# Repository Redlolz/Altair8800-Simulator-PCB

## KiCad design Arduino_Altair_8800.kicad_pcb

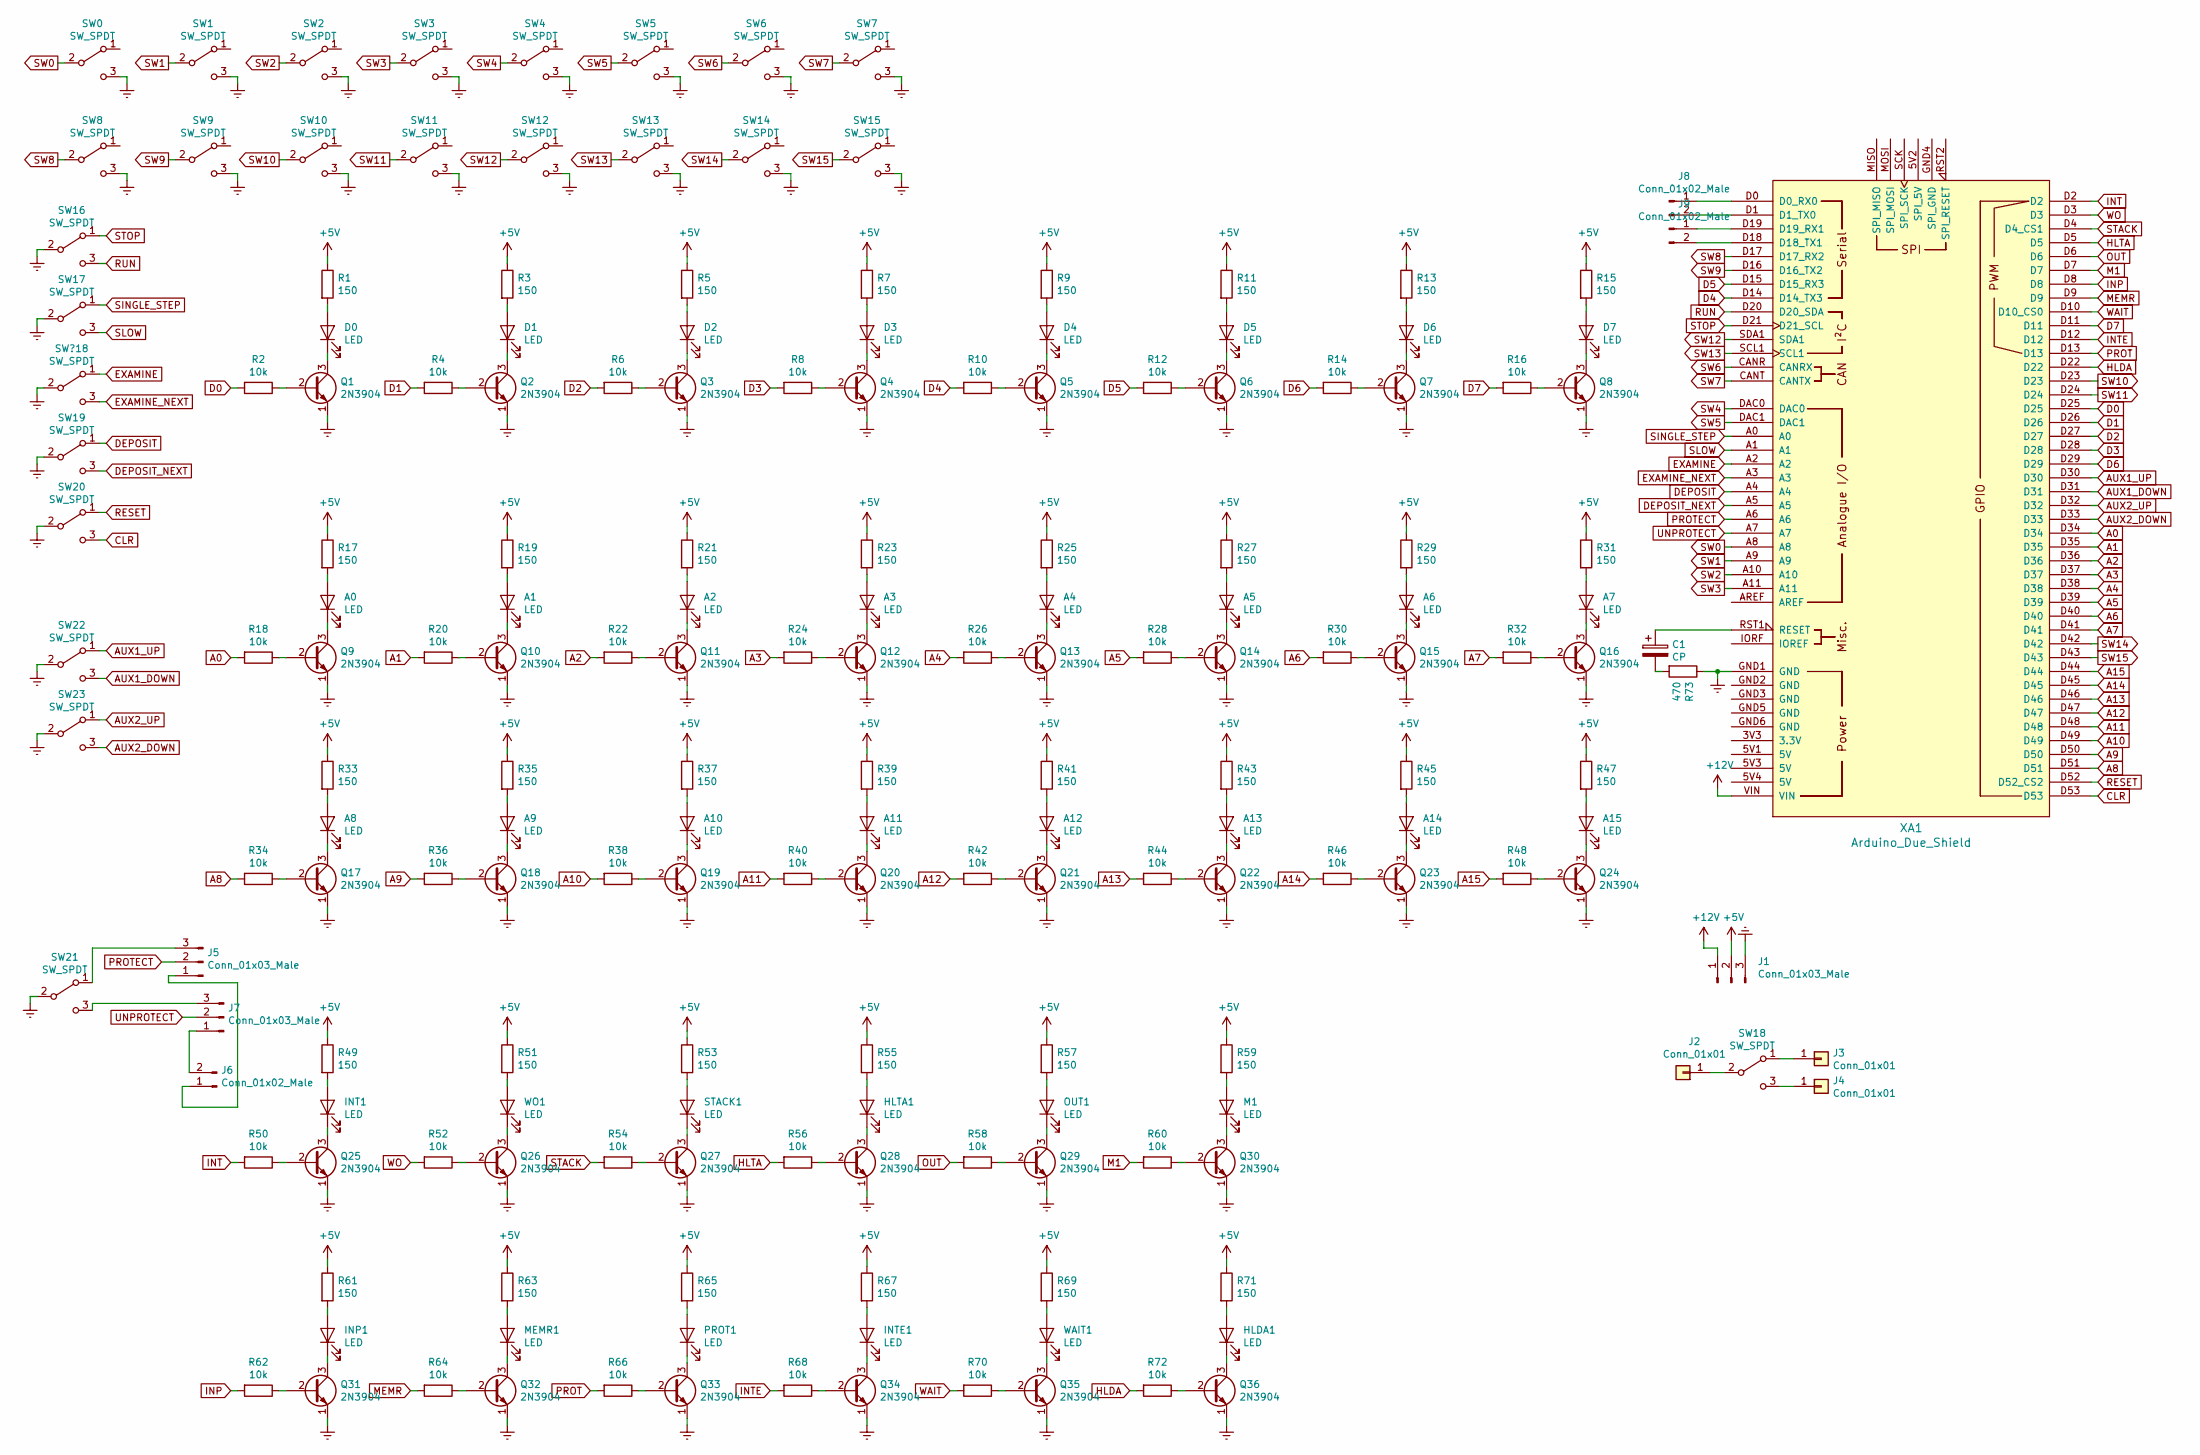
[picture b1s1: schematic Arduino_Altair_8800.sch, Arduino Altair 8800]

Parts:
A0, A1, A2, A3, A4, A5, A6, A7, A8, A9, A10, A11, A12, A13, A14, A15: LED; LED_D5.0mm
C1: CP; CP_Radial_D4.0mm_P1.50mm
D0, D1, D2, D3, D4, D5, D6, D7: LED; LED_D5.0mm
HLDA1: LED; LED_D5.0mm
HLTA1: LED; LED_D5.0mm
INP1: LED; LED_D5.0mm
INT1: LED; LED_D5.0mm
INTE1: LED; LED_D5.0mm
J1: Conn_01x03_Male; PinSocket_1x03_P2.54mm_Vertical
J2, J3, J4: Conn_01x01; SolderWirePad_1x01_Drill2mm
J5, J7: Conn_01x03_Male; PinHeader_1x03_P2.54mm_Vertical
J6, J8, J9: Conn_01x02_Male; PinHeader_1x02_P2.54mm_Vertical
M1: LED; LED_D5.0mm
MEMR1: LED; LED_D5.0mm
OUT1: LED; LED_D5.0mm
PROT1: LED; LED_D5.0mm
Q1, Q2, Q3, Q4, Q5, Q6, Q7, Q8, Q9, Q10, Q11, Q12, Q13, Q14, Q15, Q16, Q17, Q18, Q19, Q20, Q21, Q22, Q23, Q24, Q25, Q26, Q27, Q28, Q29, Q30, Q31, Q32, Q33, Q34, Q35, Q36: 2N3904; TO-92_Inline
R1, R3, R5, R7, R9, R11, R13, R15, R17, R19, R21, R23, R25, R27, R29, R31, R33, R35, R37, R39, R41, R43, R45, R47, R49, R51, R53, R55, R57, R59, R61, R63, R65, R67, R69, R71: 150; R_Axial_DIN0207_L6.3mm_D2.5mm_P7.62mm_Horizontal
R2, R4, R6, R8, R10, R12, R14, R16, R18, R20, R22, R24, R26, R28, R30, R32, R34, R36, R38, R40, R42, R44, R46, R48, R50, R52, R54, R56, R58, R60, R62, R64, R66, R68, R70, R72: 10k; R_Axial_DIN0207_L6.3mm_D2.5mm_P7.62mm_Horizontal
R73: 470; R_Axial_DIN0207_L6.3mm_D2.5mm_P7.62mm_Horizontal
STACK1: LED; LED_D5.0mm
SW0, SW1, SW2, SW3, SW4, SW5, SW6, SW7, SW8, SW9, SW10, SW11, SW12, SW13, SW14, SW15, SW16, SW17, SW18, SW19, SW20, SW21, SW22, SW23: SW_SPDT; SPDT_TOGGLE_SW
SW?18: SW_SPDT; SPDT_TOGGLE_SW
WAIT1: LED; LED_D5.0mm
WO1: LED; LED_D5.0mm
XA1: Arduino_Due_Shield

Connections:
+5V: J1.2, R1.1, R3.1, R5.1, R7.1, R9.1, R11.1, R13.1, R15.1, R17.1, R19.1, R21.1, R23.1, R25.1, R27.1, R29.1, R31.1, R33.1, R35.1, R37.1, R39.1, R41.1, R43.1, R45.1, R47.1, R49.1, R51.1, R53.1, R55.1, R57.1, R59.1, R61.1, R63.1, R65.1, R67.1, R69.1, R71.1
+12V: J1.1, XA1.VIN
A0: R18.2, XA1.D34
A1: R20.2, XA1.D35
A2: R22.2, XA1.D36
A3: R24.2, XA1.D37
A4: R26.2, XA1.D38
A5: R28.2, XA1.D39
A6: R30.2, XA1.D40
A7: R32.2, XA1.D41
A8: R34.2, XA1.D51
A9: R36.2, XA1.D50
A10: R38.2, XA1.D49
A11: R40.2, XA1.D48
A12: R42.2, XA1.D47
A13: R44.2, XA1.D46
A14: R46.2, XA1.D45
A15: R48.2, XA1.D44
AUX1_DOWN: SW22.3 (C), XA1.D31
AUX1_UP: SW22.1 (A), XA1.D30
AUX2_DOWN: SW23.3 (C), XA1.D33
AUX2_UP: SW23.1 (A), XA1.D32
CLR: SW20.3 (C), XA1.D53
D0: R2.2, XA1.D25
D1: R4.2, XA1.D26
D2: R6.2, XA1.D27
D3: R8.2, XA1.D28
D4: R10.2, XA1.D14 (D14_TX3)
D5: R12.2, XA1.D15 (D15_RX3)
D6: R14.2, XA1.D29
D7: R16.2, XA1.D11
DEPOSIT: SW19.1 (A), XA1.A4
DEPOSIT_NEXT: SW19.3 (C), XA1.A5
EXAMINE: SW?18.1 (A), XA1.A2
EXAMINE_NEXT: SW?18.3 (C), XA1.A3
Earth: J1.3, Q1.1 (E), Q2.1 (E), Q3.1 (E), Q4.1 (E), Q5.1 (E), Q6.1 (E), Q7.1 (E), Q8.1 (E), Q9.1 (E), Q10.1 (E), Q11.1 (E), Q12.1 (E), Q13.1 (E), Q14.1 (E), Q15.1 (E), Q16.1 (E), Q17.1 (E), Q18.1 (E), Q19.1 (E), Q20.1 (E), Q21.1 (E), Q22.1 (E), Q23.1 (E), Q24.1 (E), Q25.1 (E), Q26.1 (E), Q27.1 (E), Q28.1 (E), Q29.1 (E), Q30.1 (E), Q31.1 (E), Q32.1 (E), Q33.1 (E), Q34.1 (E), Q35.1 (E), Q36.1 (E), R73.1, SW0.3 (C), SW1.3 (C), SW2.3 (C), SW3.3 (C), SW4.3 (C), SW5.3 (C), SW6.3 (C), SW7.3 (C), SW8.3 (C), SW9.3 (C), SW10.3 (C), SW11.3 (C), SW12.3 (C), SW13.3 (C), SW14.3 (C), SW15.3 (C), SW16.2 (B), SW17.2 (B), SW19.2 (B), SW20.2 (B), SW21.2 (B), SW22.2 (B), SW23.2 (B), SW?18.2 (B), XA1.GND1 (GND)
HLDA: R72.2, XA1.D22
HLTA: R56.2, XA1.D5
INP: R62.2, XA1.D8
INT: R50.2, XA1.D2
INTE: R68.2, XA1.D12
M1: R60.2, XA1.D7
MEMR: R64.2, XA1.D9
unnamed: A0.1 (K), Q9.3 (C)
unnamed: A0.2 (A), R17.2
unnamed: A1.1 (K), Q10.3 (C)
unnamed: A1.2 (A), R19.2
unnamed: A2.1 (K), Q11.3 (C)
unnamed: A2.2 (A), R21.2
unnamed: A3.1 (K), Q12.3 (C)
unnamed: A3.2 (A), R23.2
unnamed: A4.1 (K), Q13.3 (C)
unnamed: A4.2 (A), R25.2
unnamed: A5.1 (K), Q14.3 (C)
unnamed: A5.2 (A), R27.2
unnamed: A6.1 (K), Q15.3 (C)
unnamed: A6.2 (A), R29.2
unnamed: A7.1 (K), Q16.3 (C)
unnamed: A7.2 (A), R31.2
unnamed: A8.1 (K), Q17.3 (C)
unnamed: A8.2 (A), R33.2
unnamed: A9.1 (K), Q18.3 (C)
unnamed: A9.2 (A), R35.2
unnamed: A10.1 (K), Q19.3 (C)
unnamed: A10.2 (A), R37.2
unnamed: A11.1 (K), Q20.3 (C)
unnamed: A11.2 (A), R39.2
unnamed: A12.1 (K), Q21.3 (C)
unnamed: A12.2 (A), R41.2
unnamed: A13.1 (K), Q22.3 (C)
unnamed: A13.2 (A), R43.2
unnamed: A14.1 (K), Q23.3 (C)
unnamed: A14.2 (A), R45.2
unnamed: A15.1 (K), Q24.3 (C)
unnamed: A15.2 (A), R47.2
unnamed: C1.1, XA1.RST1 (RESET)
unnamed: C1.2, R73.2
unnamed: D0.1 (K), Q1.3 (C)
unnamed: D0.2 (A), R1.2
unnamed: D1.1 (K), Q2.3 (C)
unnamed: D1.2 (A), R3.2
unnamed: D2.1 (K), Q3.3 (C)
unnamed: D2.2 (A), R5.2
unnamed: D3.1 (K), Q4.3 (C)
unnamed: D3.2 (A), R7.2
unnamed: D4.1 (K), Q5.3 (C)
unnamed: D4.2 (A), R9.2
unnamed: D5.1 (K), Q6.3 (C)
unnamed: D5.2 (A), R11.2
unnamed: D6.1 (K), Q7.3 (C)
unnamed: D6.2 (A), R13.2
unnamed: D7.1 (K), Q8.3 (C)
unnamed: D7.2 (A), R15.2
unnamed: HLDA1.1 (K), Q36.3 (C)
unnamed: HLDA1.2 (A), R71.2
unnamed: HLTA1.1 (K), Q28.3 (C)
unnamed: HLTA1.2 (A), R55.2
unnamed: INP1.1 (K), Q31.3 (C)
unnamed: INP1.2 (A), R61.2
unnamed: INT1.1 (K), Q25.3 (C)
unnamed: INT1.2 (A), R49.2
unnamed: INTE1.1 (K), Q34.3 (C)
unnamed: INTE1.2 (A), R67.2
unnamed: J2.1, SW18.2 (B)
unnamed: J3.1, SW18.1 (A)
unnamed: J4.1, SW18.3 (C)
unnamed: J5.1, J6.1
unnamed: J5.3, SW21.1 (A)
unnamed: J6.2, J7.1
unnamed: J7.3, SW21.3 (C)
unnamed: J8.1, XA1.D0 (D0_RX0)
unnamed: J8.2, XA1.D1 (D1_TX0)
unnamed: J9.1, XA1.D19 (D19_RX1)
unnamed: J9.2, XA1.D18 (D18_TX1)
unnamed: M1.1 (K), Q30.3 (C)
unnamed: M1.2 (A), R59.2
unnamed: MEMR1.1 (K), Q32.3 (C)
unnamed: MEMR1.2 (A), R63.2
unnamed: OUT1.1 (K), Q29.3 (C)
unnamed: OUT1.2 (A), R57.2
unnamed: PROT1.1 (K), Q33.3 (C)
unnamed: PROT1.2 (A), R65.2
unnamed: Q1.2 (B), R2.1
unnamed: Q2.2 (B), R4.1
unnamed: Q3.2 (B), R6.1
unnamed: Q4.2 (B), R8.1
unnamed: Q5.2 (B), R10.1
unnamed: Q6.2 (B), R12.1
unnamed: Q7.2 (B), R14.1
unnamed: Q8.2 (B), R16.1
unnamed: Q9.2 (B), R18.1
unnamed: Q10.2 (B), R20.1
unnamed: Q11.2 (B), R22.1
unnamed: Q12.2 (B), R24.1
unnamed: Q13.2 (B), R26.1
unnamed: Q14.2 (B), R28.1
unnamed: Q15.2 (B), R30.1
unnamed: Q16.2 (B), R32.1
unnamed: Q17.2 (B), R34.1
unnamed: Q18.2 (B), R36.1
unnamed: Q19.2 (B), R38.1
unnamed: Q20.2 (B), R40.1
unnamed: Q21.2 (B), R42.1
unnamed: Q22.2 (B), R44.1
unnamed: Q23.2 (B), R46.1
unnamed: Q24.2 (B), R48.1
unnamed: Q25.2 (B), R50.1
unnamed: Q26.2 (B), R52.1
unnamed: Q26.3 (C), WO1.1 (K)
unnamed: Q27.2 (B), R54.1
unnamed: Q27.3 (C), STACK1.1 (K)
unnamed: Q28.2 (B), R56.1
unnamed: Q29.2 (B), R58.1
unnamed: Q30.2 (B), R60.1
unnamed: Q31.2 (B), R62.1
unnamed: Q32.2 (B), R64.1
unnamed: Q33.2 (B), R66.1
unnamed: Q34.2 (B), R68.1
unnamed: Q35.2 (B), R70.1
unnamed: Q35.3 (C), WAIT1.1 (K)
unnamed: Q36.2 (B), R72.1
unnamed: R51.2, WO1.2 (A)
unnamed: R53.2, STACK1.2 (A)
unnamed: R69.2, WAIT1.2 (A)
OUT: R58.2, XA1.D6
PROT: R66.2, XA1.D13
PROTECT: J5.2, XA1.A6
RESET: SW20.1 (A), XA1.D52 (D52_CS2)
RUN: SW16.3 (C), XA1.D20 (D20_SDA)
SINGLE_STEP: SW17.1 (A), XA1.A0
SLOW: SW17.3 (C), XA1.A1
STACK: R54.2, XA1.D4 (D4_CS1)
STOP: SW16.1 (A), XA1.D21 (D21_SCL)
SW0: SW0.2 (B), XA1.A8
SW1: SW1.2 (B), XA1.A9
SW2: SW2.2 (B), XA1.A10
SW3: SW3.2 (B), XA1.A11
SW4: SW4.2 (B), XA1.DAC0
SW5: SW5.2 (B), XA1.DAC1
SW6: SW6.2 (B), XA1.CANR (CANRX)
SW7: SW7.2 (B), XA1.CANT (CANTX)
SW8: SW8.2 (B), XA1.D17 (D17_RX2)
SW9: SW9.2 (B), XA1.D16 (D16_TX2)
SW10: SW10.2 (B), XA1.D23
SW11: SW11.2 (B), XA1.D24
SW12: SW12.2 (B), XA1.SDA1
SW13: SW13.2 (B), XA1.SCL1
SW14: SW14.2 (B), XA1.D42
SW15: SW15.2 (B), XA1.D43
UNPROTECT: J7.2, XA1.A7
WAIT: R70.2, XA1.D10 (D10_CS0)
WO: R52.2, XA1.D3

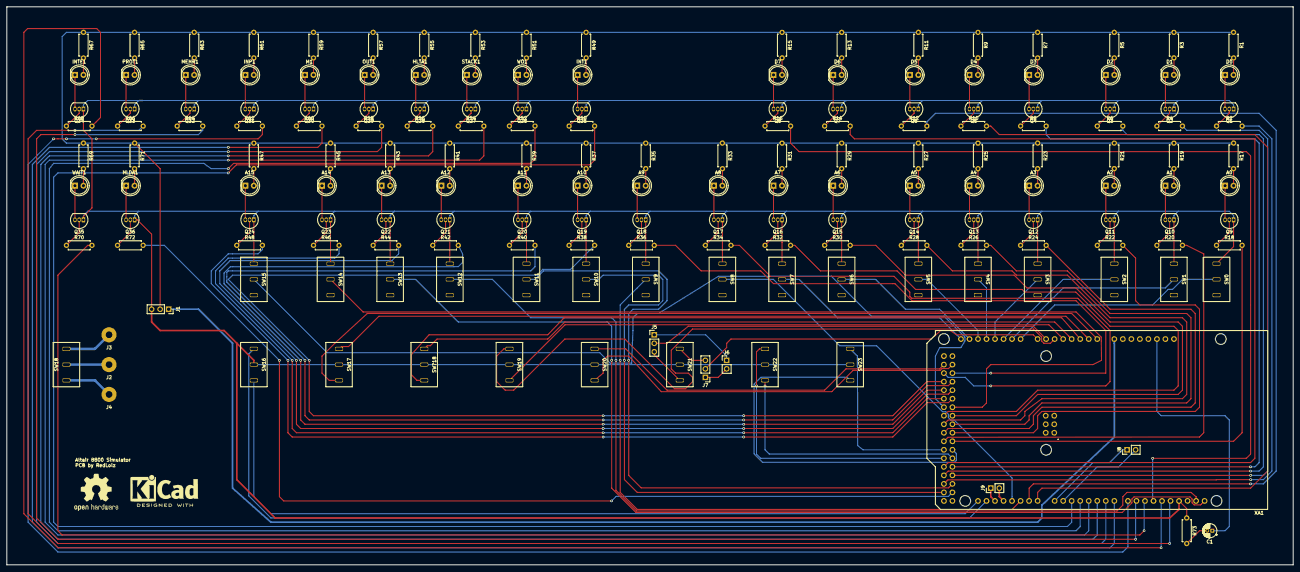
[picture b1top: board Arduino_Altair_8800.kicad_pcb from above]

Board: 2 copper layers, 383.5 x 166.4 mm, 181 parts (0 on the bottom side), 192 nets.

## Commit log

2019-08-06 Create LICENSE
